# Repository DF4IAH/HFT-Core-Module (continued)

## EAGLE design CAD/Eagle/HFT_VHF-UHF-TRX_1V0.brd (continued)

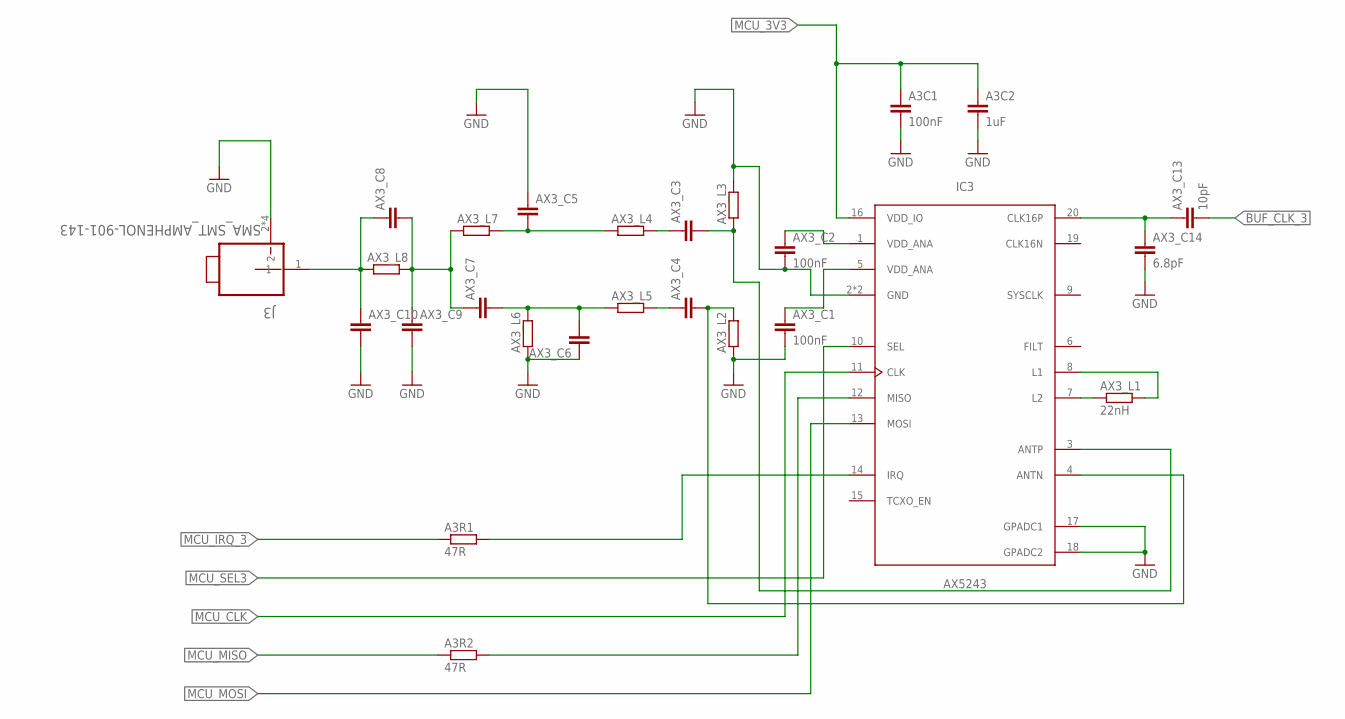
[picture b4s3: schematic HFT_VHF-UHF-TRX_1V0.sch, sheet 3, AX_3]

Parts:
A3C1: 100nF; C0805
A3C2: 1uF; C0805
A3R1, A3R2: 47R; R0805
AX3_C1, AX3_C2: 100nF; C0805
AX3_C3, AX3_C4, AX3_C5, AX3_C6, AX3_C7, AX3_C8, AX3_C9, AX3_C10: C-EUC0805; C0805
AX3_C13: 10pF; C0805
AX3_C14: 6.8pF; C0805
AX3_L1: 22nH; R0805
AX3_L2, AX3_L3, AX3_L4, AX3_L5, AX3_L6, AX3_L7, AX3_L8: R-EU_R0805; R0805
IC3: AX5243; QFN20-4X4-0P5-PAD
J3: SMA_SMT_AMPHENOL-901-143; SMA_SMT_AMPHENOL_901-143

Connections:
AX3_C3_L4: AX3_C3.1, AX3_L4.2
AX3_C4_L5: AX3_C4.1, AX3_L5.2
AX3_CH3_ANA1: AX3_C2.1, IC3.1 (VDD_ANA)
AX3_CH3_ANA2: AX3_C1.1, IC3.5 (VDD_ANA)
AX3_CH3_ANTN: AX3_C4.2, AX3_L2.2, IC3.4 (ANTN)
AX3_CH3_ANTP: AX3_C3.2, AX3_L3.1, IC3.3 (ANTP)
AX3_CH_3: AX3_C8.1, AX3_C10.1, AX3_L8.1, J3.1
AX3_IRQ_3: A3R1.2, IC3.14 (IRQ)
AX3_L1: AX3_L1.2, IC3.8 (L1)
AX3_L2: AX3_L1.1, IC3.7 (L2)
AX3_L4_C5_L7: AX3_C5.2, AX3_L4.1, AX3_L7.2
AX3_L4_C7_L8: AX3_C7.1, AX3_C8.2, AX3_C9.1, AX3_L7.1, AX3_L8.2
AX3_L5_C6_L6_C7: AX3_C6.2, AX3_C7.2, AX3_L5.1, AX3_L6.2
AX3_MISO: A3R2.2, IC3.12 (MISO)
BUF_CLK_3: AX3_C13.2; also elsewhere on the board
BUF_CLK_A3: AX3_C13.1, AX3_C14.1, IC3.20 (CLK16P)
GND: A3C1.2, A3C2.2, AX3_C1.2, AX3_C2.2, AX3_C5.1, AX3_C6.1, AX3_C9.2, AX3_C10.2, AX3_C14.2, AX3_L2.1, AX3_L3.2, AX3_L6.1, IC3.2 (GND), IC3.17 (GPADC1), IC3.18 (GPADC2), IC3.21 (GND), J3.2, J3.3 (2), J3.4 (2), J3.5 (2); also elsewhere on the board
MCU_3V3: A3C1.1, A3C2.1, IC3.16 (VDD_IO); also elsewhere on the board
MCU_CLK: IC3.11 (CLK); also elsewhere on the board
MCU_IRQ_3: A3R1.1; also elsewhere on the board
MCU_MISO: A3R2.1; also elsewhere on the board
MCU_MOSI: IC3.13 (MOSI); also elsewhere on the board
MCU_SEL3: IC3.10 (SEL); also elsewhere on the board

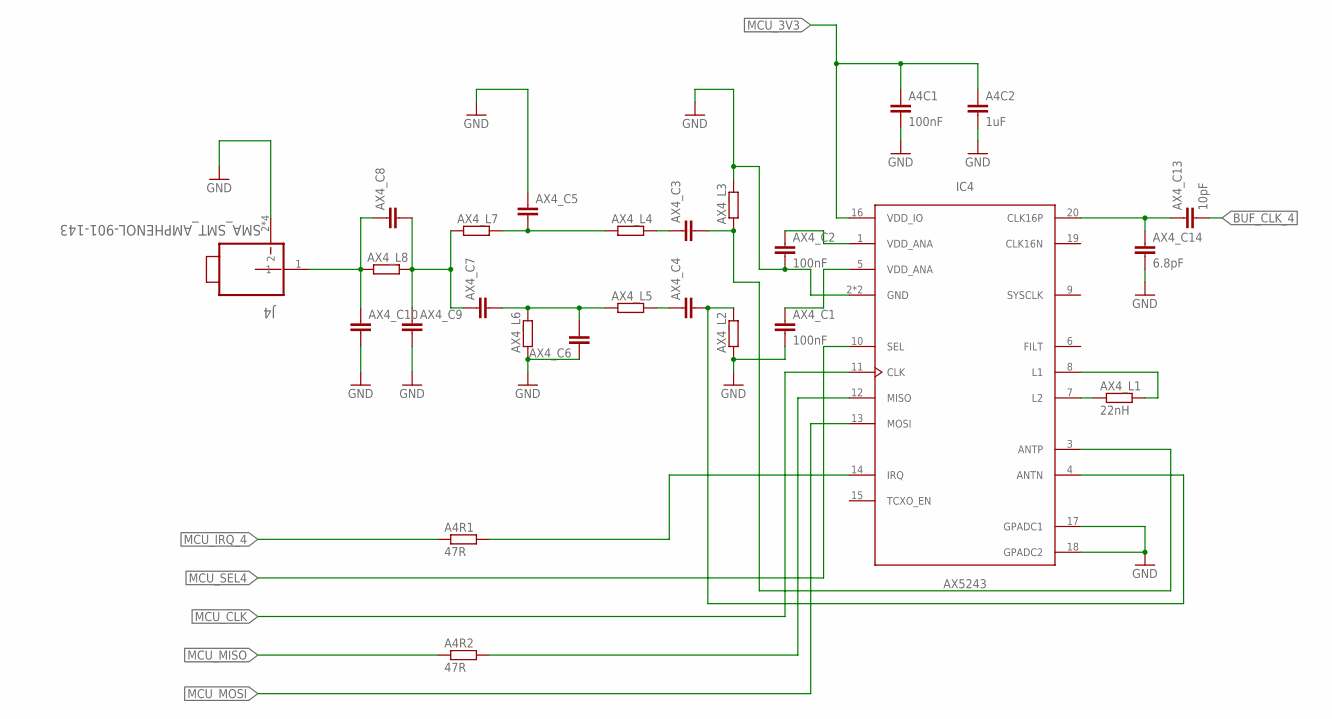
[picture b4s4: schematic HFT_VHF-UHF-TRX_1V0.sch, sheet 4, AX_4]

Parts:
A4C1: 100nF; C0805
A4C2: 1uF; C0805
A4R1, A4R2: 47R; R0805
AX4_C1, AX4_C2: 100nF; C0805
AX4_C3, AX4_C4, AX4_C5, AX4_C6, AX4_C7, AX4_C8, AX4_C9, AX4_C10: C-EUC0805; C0805
AX4_C13: 10pF; C0805
AX4_C14: 6.8pF; C0805
AX4_L1: 22nH; R0805
AX4_L2, AX4_L3, AX4_L4, AX4_L5, AX4_L6, AX4_L7, AX4_L8: R-EU_R0805; R0805
IC4: AX5243; QFN20-4X4-0P5-PAD
J4: SMA_SMT_AMPHENOL-901-143; SMA_SMT_AMPHENOL_901-143

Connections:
AX4_C3_L4: AX4_C3.1, AX4_L4.2
AX4_C4_L5: AX4_C4.1, AX4_L5.2
AX4_CH4_ANA1: AX4_C2.1, IC4.1 (VDD_ANA)
AX4_CH4_ANA2: AX4_C1.1, IC4.5 (VDD_ANA)
AX4_CH4_ANTN: AX4_C4.2, AX4_L2.2, IC4.4 (ANTN)
AX4_CH4_ANTP: AX4_C3.2, AX4_L3.1, IC4.3 (ANTP)
AX4_CH_4: AX4_C8.1, AX4_C10.1, AX4_L8.1, J4.1
AX4_IRQ_4: A4R1.2, IC4.14 (IRQ)
AX4_L1: AX4_L1.2, IC4.8 (L1)
AX4_L2: AX4_L1.1, IC4.7 (L2)
AX4_L4_C5_L7: AX4_C5.2, AX4_L4.1, AX4_L7.2
AX4_L4_C7_L8: AX4_C7.1, AX4_C8.2, AX4_C9.1, AX4_L7.1, AX4_L8.2
AX4_L5_C6_L6_C7: AX4_C6.2, AX4_C7.2, AX4_L5.1, AX4_L6.2
AX4_MISO: A4R2.2, IC4.12 (MISO)
BUF_CLK_4: AX4_C13.2; also elsewhere on the board
BUF_CLK_A4: AX4_C13.1, AX4_C14.1, IC4.20 (CLK16P)
GND: A4C1.2, A4C2.2, AX4_C1.2, AX4_C2.2, AX4_C5.1, AX4_C6.1, AX4_C9.2, AX4_C10.2, AX4_C14.2, AX4_L2.1, AX4_L3.2, AX4_L6.1, IC4.2 (GND), IC4.17 (GPADC1), IC4.18 (GPADC2), IC4.21 (GND), J4.2, J4.3 (2), J4.4 (2), J4.5 (2); also elsewhere on the board
MCU_3V3: A4C1.1, A4C2.1, IC4.16 (VDD_IO); also elsewhere on the board
MCU_CLK: IC4.11 (CLK); also elsewhere on the board
MCU_IRQ_4: A4R1.1; also elsewhere on the board
MCU_MISO: A4R2.1; also elsewhere on the board
MCU_MOSI: IC4.13 (MOSI); also elsewhere on the board
MCU_SEL4: IC4.10 (SEL); also elsewhere on the board

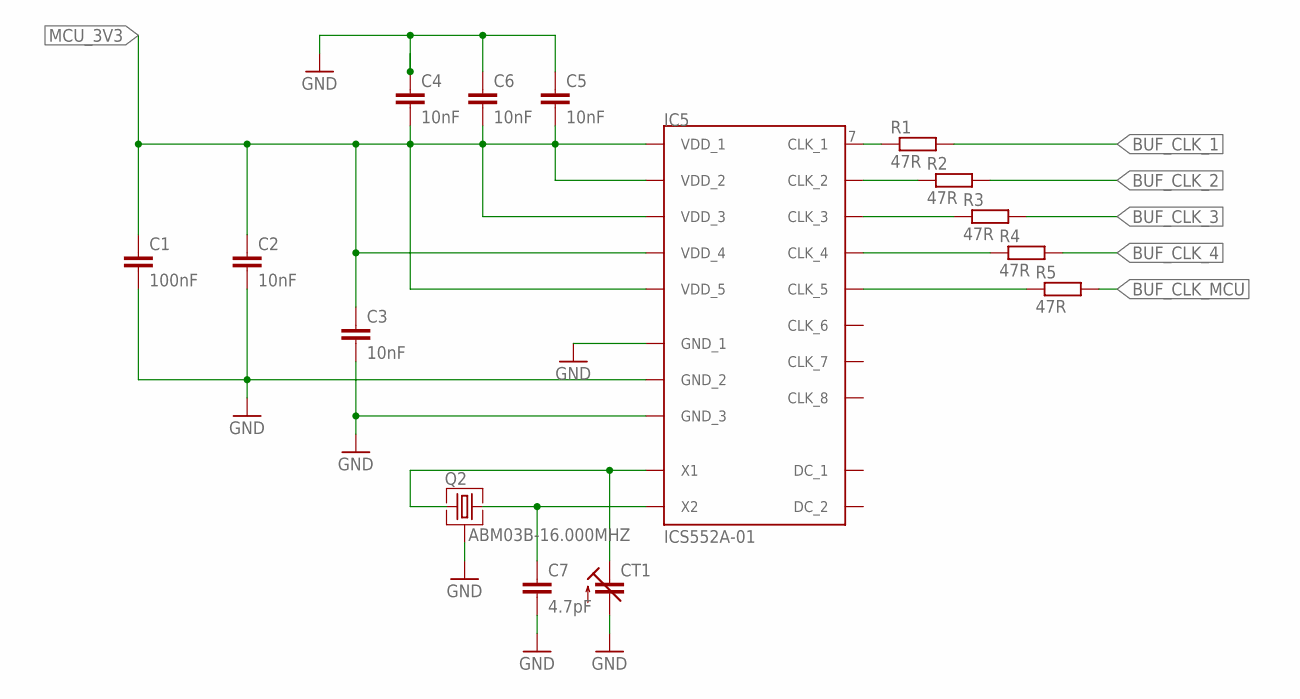
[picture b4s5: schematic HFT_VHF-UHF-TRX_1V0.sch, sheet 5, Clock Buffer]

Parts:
C1: 100nF; C0805
C2, C3, C4, C5, C6: 10nF; C0805
C7: 4.7pF; C0805
CT1: C-TRIMM3MM2_2MM5; 3MM2_X_2MM5
IC5: ICS552A-01; SSOP20
Q2: ABM03B-16.000MHZ; ABM03B
R1, R2, R3, R4, R5: 47R; R0805

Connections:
BUFF_X1: CT1.- (E), IC5.3 (X1), Q2.1
BUFF_X2: C7.1, IC5.2 (X2), Q2.3 (2)
BUF_CLK_1: R1.2; also elsewhere on the board
BUF_CLK_2: R2.2; also elsewhere on the board
BUF_CLK_3: R3.2; also elsewhere on the board
BUF_CLK_4: R4.2; also elsewhere on the board
BUF_CLK_MCU: R5.2; also elsewhere on the board
BUF_O_CLK_1: IC5.7 (CLK_1), R1.1
BUF_O_CLK_2: IC5.8 (CLK_2), R2.1
BUF_O_CLK_3: IC5.9 (CLK_3), R3.1
BUF_O_CLK_4: IC5.10 (CLK_4), R4.1
BUF_O_CLK_MCU: IC5.12 (CLK_5), R5.1
GND: C1.2, C2.2, C3.2, C4.1, C5.1, C6.1, C7.2, CT1.+ (A), IC5.5 (GND_1), IC5.6 (GND_2), IC5.14 (GND_3), Q2.2 (3), Q2.4 (3); also elsewhere on the board
MCU_3V3: C1.1, C2.1, C3.1, C4.2, C5.2, C6.2, IC5.4 (VDD_1), IC5.11 (VDD_2), IC5.15 (VDD_3), IC5.16 (VDD_4), IC5.20 (VDD_5); also elsewhere on the board

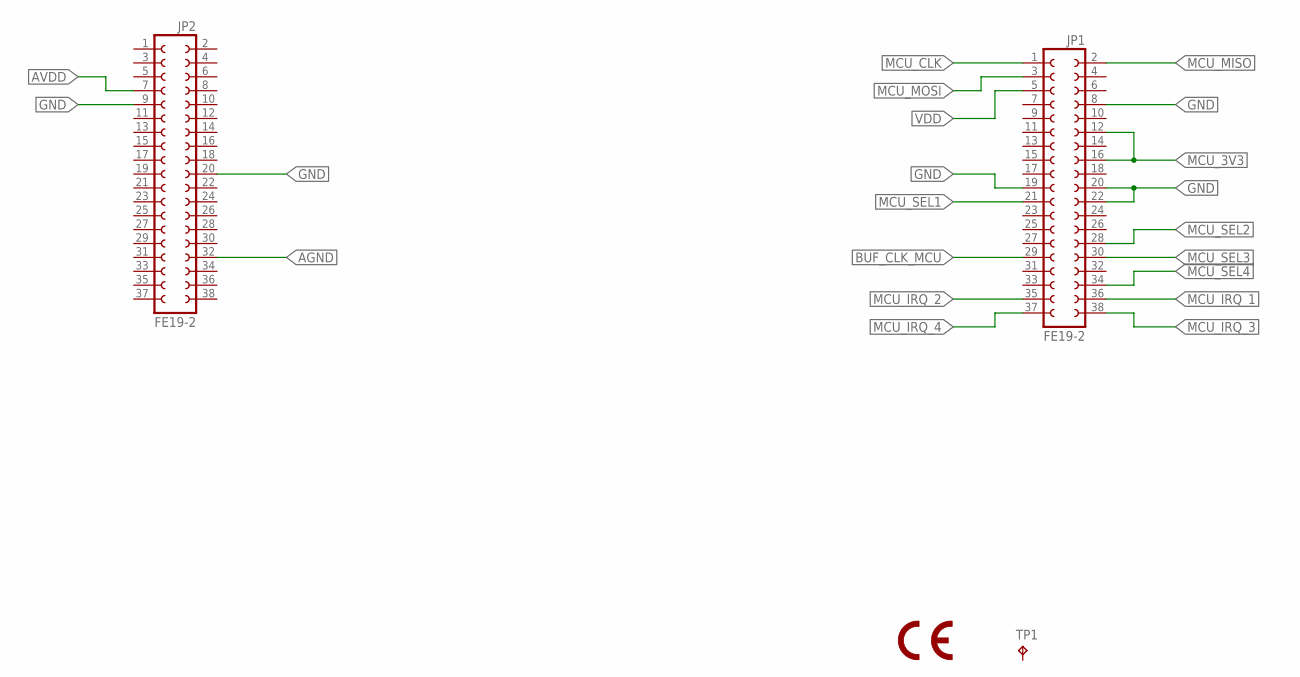
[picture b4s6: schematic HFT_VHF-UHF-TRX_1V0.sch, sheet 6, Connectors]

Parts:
JP1, JP2: FE19-2
TP1: TPB1,27; B1,27

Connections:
AGND: JP2.32
AVDD: JP2.7
BUF_CLK_MCU: JP1.29; also elsewhere on the board
GND: JP1.8, JP1.19, JP1.20, JP1.22, JP2.9, JP2.20; also elsewhere on the board
MCU_3V3: JP1.12, JP1.16; also elsewhere on the board
MCU_CLK: JP1.1; also elsewhere on the board
MCU_IRQ_1: JP1.36; also elsewhere on the board
MCU_IRQ_2: JP1.35; also elsewhere on the board
MCU_IRQ_3: JP1.38; also elsewhere on the board
MCU_IRQ_4: JP1.37; also elsewhere on the board
MCU_MISO: JP1.2; also elsewhere on the board
MCU_MOSI: JP1.3; also elsewhere on the board
MCU_SEL1: JP1.21; also elsewhere on the board
MCU_SEL2: JP1.28; also elsewhere on the board
MCU_SEL3: JP1.30; also elsewhere on the board
MCU_SEL4: JP1.34; also elsewhere on the board
VDD: JP1.5

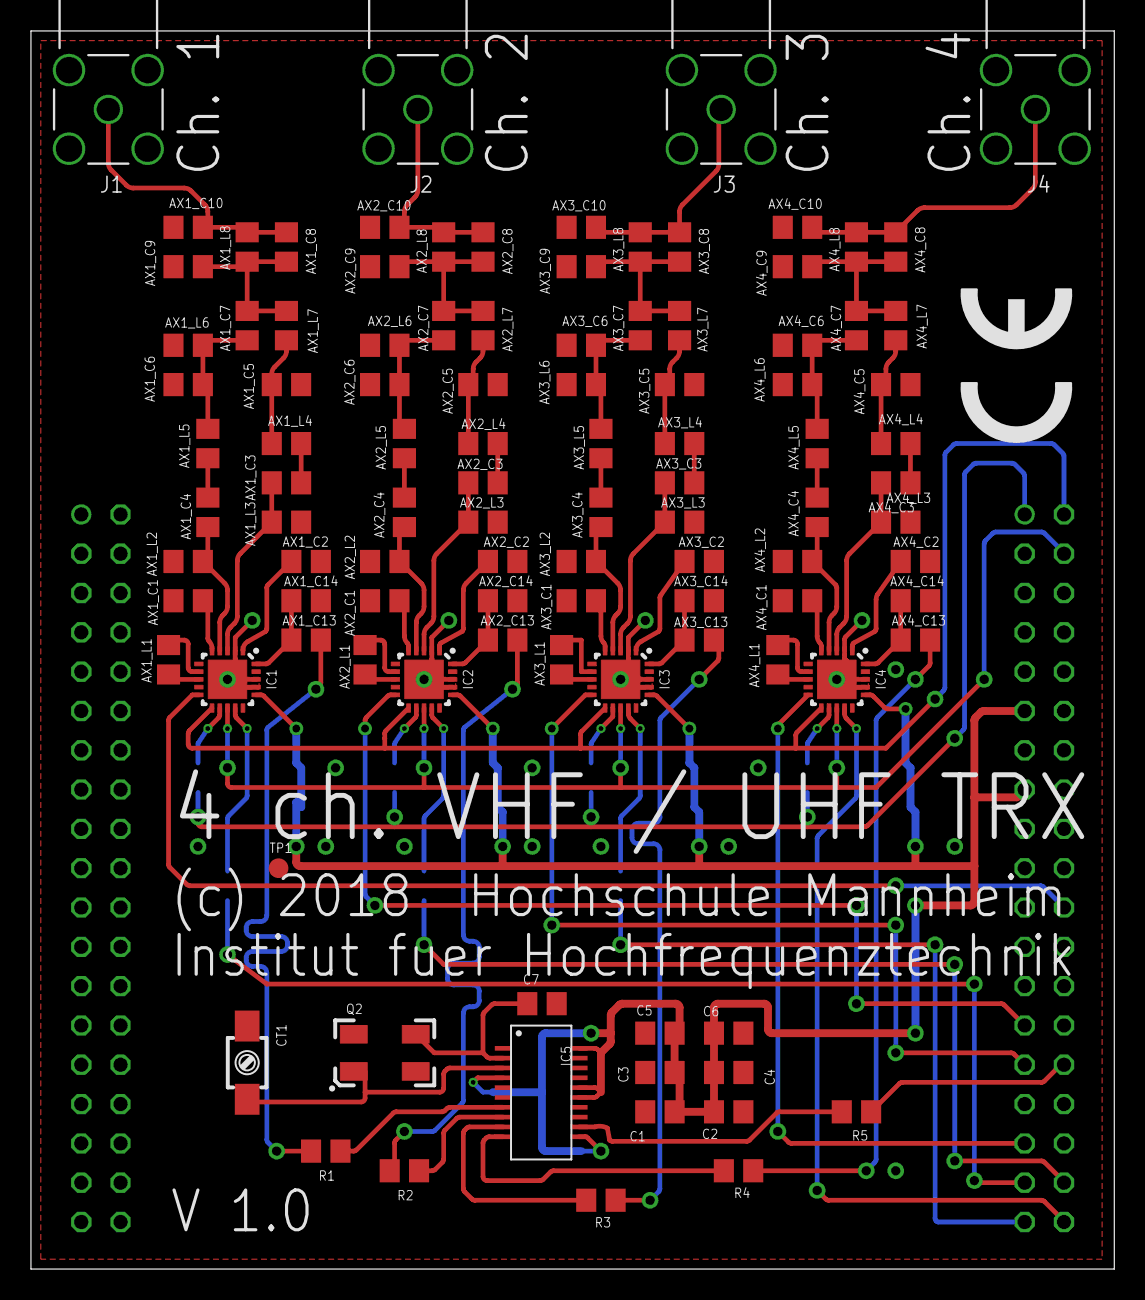
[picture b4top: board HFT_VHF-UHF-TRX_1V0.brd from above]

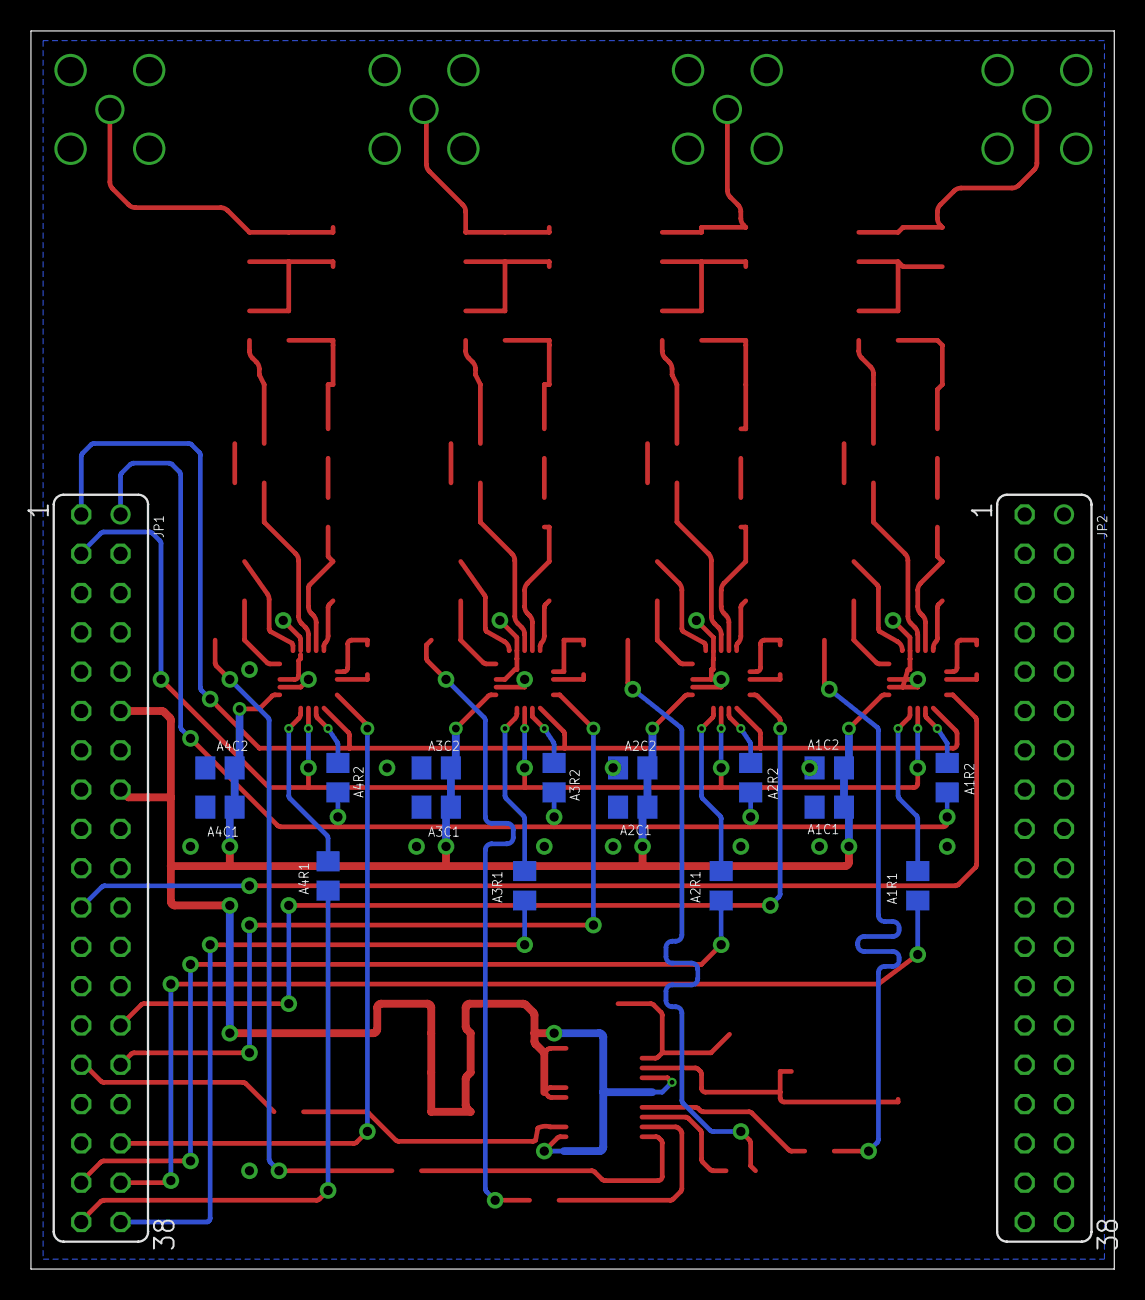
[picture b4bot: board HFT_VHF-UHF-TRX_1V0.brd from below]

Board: 2 copper layers, 70.0 x 80.0 mm, 123 parts (18 on the bottom side), 85 nets.

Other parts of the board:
X_CE_LOGO: CE_7.3MM

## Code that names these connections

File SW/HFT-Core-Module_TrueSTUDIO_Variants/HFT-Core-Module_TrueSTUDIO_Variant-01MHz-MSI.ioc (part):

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Mcu.Name=STM32L496ZGTxP
Mcu.Package=LQFP144
Mcu.UserName=STM32L496ZGTxP
PA0.GPIOParameters=GPIO_Speed,GPIO_PuPd,GPIO_Label
PA0.GPIO_Label=UART2_CTS_IN
PA0.GPIO_PuPd=GPIO_PULLDOWN
PA0.GPIO_Speed=GPIO_SPEED_FREQ_LOW
PA0.Mode=CTS_RTS
PA0.Signal=USART2_CTS
PA11.GPIOParameters=GPIO_Speed,GPIO_PuPd,GPIO_Label
PA11.GPIO_Label=PA_USB_N
PA11.GPIO_PuPd=GPIO_NOPULL
PA11.GPIO_Speed=GPIO_SPEED_FREQ_HIGH
PA11.Signal=USB_OTG_FS_DM
PA12.GPIOParameters=GPIO_Speed,GPIO_PuPd,GPIO_Label
PA12.GPIO_Label=PA_USB_P
PA12.GPIO_PuPd=GPIO_NOPULL
PA12.GPIO_Speed=GPIO_SPEED_FREQ_HIGH
PA12.Signal=USB_OTG_FS_DP
PA13\ (JTMS/SWDIO).GPIOParameters=GPIO_Label
PA13\ (JTMS/SWDIO).GPIO_Label=MCU_INOUT_SWDIO
PA13\ (JTMS/SWDIO).Mode=Serial_Wire
PA13\ (JTMS/SWDIO).Signal=SYS_JTMS-SWDIO
PA14\ (JTCK/SWCLK).GPIOParameters=GPIO_Label
PA14\ (JTCK/SWCLK).GPIO_Label=MCU_IN_SWCLK
PA14\ (JTCK/SWCLK).Mode=Serial_Wire
PA14\ (JTCK/SWCLK).Signal=SYS_JTCK-SWCLK
PA2.GPIOParameters=GPIO_Speed,GPIO_PuPd,GPIO_Label
PA2.GPIO_Label=UART2_TX_OUT
PA2.GPIO_PuPd=GPIO_NOPULL
PA2.GPIO_Speed=GPIO_SPEED_FREQ_LOW
PA2.Mode=Asynchronous
PA2.Signal=USART2_TX
PA3.GPIOParameters=GPIO_Label
PA3.GPIO_Label=MCU_VSOL_ADC1
PA3.Signal=ADCx_IN8
PA6.GPIOParameters=GPIO_Speed,GPIO_PuPd,GPIO_Label
PA6.GPIO_Label=UART3_CTS_IN
PA6.GPIO_PuPd=GPIO_PULLDOWN
PA6.GPIO_Speed=GPIO_SPEED_FREQ_LOW
PA6.Mode=CTS_RTS
PA6.Signal=USART3_CTS
PA7.GPIOParameters=GPIO_PuPd,GPIO_Label
PA7.GPIO_Label=MCU_OUT_PWM_LED_G
PA7.GPIO_PuPd=GPIO_NOPULL
PA7.Signal=S_TIM3_CH2
PA8.GPIOParameters=GPIO_Speed,GPIO_PuPd,GPIO_Label
PA8.GPIO_Label=MCU_MCO
PA8.GPIO_PuPd=GPIO_NOPULL
PA8.GPIO_Speed=GPIO_SPEED_FREQ_LOW
PA8.Mode=Clock-out
PA8.Signal=RCC_MCO
PA9.GPIOParameters=GPIO_PuPd,GPIO_Label
PA9.GPIO_Label=MCU_IN_VBUS
PA9.GPIO_PuPd=GPIO_PULLDOWN
PA9.Signal=USB_OTG_FS_VBUS
PB0.GPIOParameters=GPIO_PuPd,GPIO_Label
PB0.GPIO_Label=MCU_OUT_PWM_LED_B
PB0.GPIO_PuPd=GPIO_NOPULL
PB0.Signal=S_TIM3_CH3
PB1.GPIOParameters=GPIO_Speed,GPIO_PuPd,GPIO_Label
PB1.GPIO_Label=UART3_RTS_OUT
PB1.GPIO_PuPd=GPIO_NOPULL
PB1.GPIO_Speed=GPIO_SPEED_FREQ_LOW
PB1.Mode=CTS_RTS
PB1.Signal=USART3_RTS
PB10.GPIOParameters=GPIO_PuPd,GPIO_Label
PB10.GPIO_Label=MCU_IN_RE_I
PB10.GPIO_PuPd=GPIO_PULLUP
PB10.Signal=GPIO_Input
PB12.GPIOParameters=GPIO_PuPd,GPIO_Label
PB12.GPIO_Label=MCU_IN_RE_Q
PB12.GPIO_PuPd=GPIO_PULLUP
PB12.Signal=GPIO_Input
PB13.GPIOParameters=GPIO_Speed,GPIO_PuPd,GPIO_Label
PB13.GPIO_Label=I2S2A_SCK_IN
PB13.GPIO_PuPd=GPIO_PULLDOWN
PB13.GPIO_Speed=GPIO_SPEED_FREQ_MEDIUM
PB13.Signal=SAI2_SCK_A
PB14.GPIOParameters=GPIO_PuPd,GPIO_Label
PB14.GPIO_Label=MCU_IN_RE_PB
PB14.GPIO_PuPd=GPIO_PULLUP
PB14.Signal=GPIO_Input
PB3\ (JTDO/TRACESWO).GPIOParameters=GPIO_PuPd,GPIO_Label
PB3\ (JTDO/TRACESWO).GPIO_Label=MCU_INOUT_PN00
PB3\ (JTDO/TRACESWO).GPIO_PuPd=GPIO_PULLDOWN
PB3\ (JTDO/TRACESWO).Signal=GPIO_Input
PB5.GPIOParameters=GPIO_PuPd,GPIO_Label
PB5.GPIO_Label=MCU_INOUT_PN01
PB5.GPIO_PuPd=GPIO_PULLDOWN
PB5.Signal=GPIO_Input
PB6.GPIOParameters=GPIO_PuPd,GPIO_Label
PB6.GPIO_Label=MCU_INOUT_PN02
PB6.GPIO_PuPd=GPIO_PULLDOWN
PB6.Signal=GPIO_Input
PB7.GPIOParameters=GPIO_PuPd,GPIO_Label
PB7.GPIO_Label=MCU_INOUT_PN03
PB7.GPIO_PuPd=GPIO_PULLDOWN
PB7.Signal=GPIO_Input
PC0.GPIOParameters=GPIO_PuPd,GPIO_Label
PC0.GPIO_Label=MCU_OUT_VDD12_EN
PC0.GPIO_PuPd=GPIO_NOPULL
PC0.Signal=GPIO_Output
PC1.GPIOParameters=GPIO_PuPd,GPIO_Label
PC1.GPIO_Label=MCU_OUT_HICUR_EN
PC1.GPIO_PuPd=GPIO_NOPULL
PC1.Signal=GPIO_Output
PC10.GPIOParameters=GPIO_Speed,GPIO_PuPd,GPIO_Label
PC10.GPIO_Label=MCU_SPI3_SCK
PC10.GPIO_PuPd=GPIO_NOPULL
PC10.GPIO_Speed=GPIO_SPEED_FREQ_VERY_HIGH
PC10.Mode=Full_Duplex_Master
PC10.Signal=SPI3_SCK
PC11.GPIOParameters=GPIO_Speed,GPIO_PuPd,GPIO_Label
PC11.GPIO_Label=MCU_SPI3_MISO
PC11.GPIO_PuPd=GPIO_PULLDOWN
PC11.GPIO_Speed=GPIO_SPEED_FREQ_VERY_HIGH
PC11.Mode=Full_Duplex_Master
PC11.Signal=SPI3_MISO
PC12.GPIOParameters=GPIO_Speed,GPIO_PuPd,GPIO_Label
PC12.GPIO_Label=MCU_SPI3_MOSI
PC12.GPIO_PuPd=GPIO_NOPULL
PC12.GPIO_Speed=GPIO_SPEED_FREQ_VERY_HIGH
PC12.Mode=Full_Duplex_Master
PC12.Signal=SPI3_MOSI
PC13.GPIOParameters=GPIO_Label
PC13.GPIO_Label=MCU_IN_WAKEUP
PC13.Mode=SYS_WakeUp1
PC13.Signal=SYS_WKUP2
PC14-OSC32_IN\ (PC14).GPIOParameters=GPIO_Label
PC14-OSC32_IN\ (PC14).GPIO_Label=MCU_OSC32_IN
PC14-OSC32_IN\ (PC14).Mode=LSE-External-Oscillator
PC14-OSC32_IN\ (PC14).Signal=RCC_OSC32_IN
PC15-OSC32_OUT\ (PC15).GPIOParameters=GPIO_Label
PC15-OSC32_OUT\ (PC15).GPIO_Label=MCU_OSC32_OUT
PC15-OSC32_OUT\ (PC15).Mode=LSE-External-Oscillator
PC15-OSC32_OUT\ (PC15).Signal=RCC_OSC32_OUT
PC2.GPIOParameters=GPIO_PuPd,GPIO_Label
PC2.GPIO_Label=MCU_OUT_VUSB_EN
PC2.GPIO_PuPd=GPIO_NOPULL
PC2.Signal=GPIO_Output
PC3.GPIOParameters=GPIO_PuPd,GPIO_Label
PC3.GPIO_Label=MCU_OUT_20MHZ_EN
PC3.GPIO_PuPd=GPIO_NOPULL
PC3.Signal=GPIO_Output
PC4.GPIOParameters=GPIO_Speed,GPIO_PuPd,GPIO_Label
PC4.GPIO_Label=UART3_TX_OUT
PC4.GPIO_PuPd=GPIO_NOPULL
PC4.GPIO_Speed=GPIO_SPEED_FREQ_LOW
PC4.Mode=Asynchronous
PC4.Signal=USART3_TX
PC5.GPIOParameters=GPIO_Speed,GPIO_PuPd,GPIO_Label
PC5.GPIO_Label=UART3_RX_IN
PC5.GPIO_PuPd=GPIO_PULLUP
PC5.GPIO_Speed=GPIO_SPEED_FREQ_LOW
PC5.Mode=Asynchronous
PC5.Signal=USART3_RX
PC6.GPIOParameters=GPIO_PuPd,GPIO_Label
PC6.GPIO_Label=MCU_OUT_PWM_LED_R
PC6.GPIO_PuPd=GPIO_NOPULL
PC6.Signal=S_TIM3_CH1
PC8.GPIOParameters=GPIO_PuPd,GPIO_Label
PC8.GPIO_Label=MCU_IN_AUDIO_DAC_nRDY
PC8.GPIO_PuPd=GPIO_PULLUP
PC8.Signal=GPIO_Input
PC9.GPIOParameters=GPIO_Speed,PinState,GPIO_PuPd,GPIO_Label
PC9.GPIO_Label=MCU_OUT_AUDIO_DAC_SEL
PC9.GPIO_PuPd=GPIO_NOPULL
PC9.GPIO_Speed=GPIO_SPEED_FREQ_VERY_HIGH
PC9.PinState=GPIO_PIN_RESET
PC9.Signal=GPIO_Output
PD0.GPIOParameters=GPIO_PuPd,GPIO_Label
PD0.GPIO_Label=MCU_IN_AUDIO_ADC_MDAT1
PD0.GPIO_PuPd=GPIO_PULLDOWN
PD0.Signal=GPIO_Input
PD1.GPIOParameters=GPIO_PuPd,GPIO_Label
PD1.GPIO_Label=MCU_IN_AUDIO_ADC_MDAT0
PD1.GPIO_PuPd=GPIO_PULLDOWN
PD1.Signal=GPIO_Input
PD10.GPIOParameters=GPIO_PuPd,GPIO_Label
PD10.GPIO_Label=MCU_INOUT_PS01
PD10.GPIO_PuPd=GPIO_PULLDOWN
PD10.Signal=GPIO_Input
PD11.GPIOParameters=GPIO_Speed,GPIO_PuPd,GPIO_Label
PD11.GPIO_Label=I2S2A_SD_IN
PD11.GPIO_PuPd=GPIO_PULLDOWN
PD11.GPIO_Speed=GPIO_SPEED_FREQ_MEDIUM
PD11.Signal=SAI2_SD_A
PD12.GPIOParameters=GPIO_Speed,GPIO_PuPd,GPIO_Label
PD12.GPIO_Label=I2S2A_FS_IN
PD12.GPIO_PuPd=GPIO_PULLDOWN
PD12.GPIO_Speed=GPIO_SPEED_FREQ_MEDIUM
PD12.Signal=SAI2_FS_A
PD13.GPIOParameters=GPIO_Speed,GPIO_PuPdOD,GPIO_Label
PD13.GPIO_Label=MCU_I2C4_SDA
PD13.GPIO_PuPdOD=GPIO_PULLUP
PD13.GPIO_Speed=GPIO_SPEED_FREQ_LOW
PD13.Mode=I2C
PD13.Signal=I2C4_SDA
PD14.GPIOParameters=GPIO_PuPd,GPIO_Label
PD14.GPIO_Label=MCU_INOUT_PS02
PD14.GPIO_PuPd=GPIO_PULLDOWN
PD14.Signal=GPIO_Input
PD15.GPIOParameters=GPIO_PuPd,GPIO_Label
PD15.GPIO_Label=MCU_INOUT_PS03
PD15.GPIO_PuPd=GPIO_PULLDOWN
PD15.Signal=GPIO_Input
PD2.GPIOParameters=GPIO_PuPd,GPIO_Label
PD2.GPIO_Label=MCU_IN_AUDIO_ADC_nDR
PD2.GPIO_PuPd=GPIO_PULLUP
PD2.Signal=GPIO_Input
PD3.GPIOParameters=GPIO_PuPd,GPIO_Label
PD3.GPIO_Label=MCU_OUT_AUDIO_ADC_nRESET
PD3.GPIO_PuPd=GPIO_NOPULL
PD3.Signal=GPIO_Output
PD4.GPIOParameters=GPIO_Speed,GPIO_PuPd,GPIO_Label
PD4.GPIO_Label=UART2_RTS_OUT
PD4.GPIO_PuPd=GPIO_NOPULL
PD4.GPIO_Speed=GPIO_SPEED_FREQ_LOW
PD4.Mode=CTS_RTS
PD4.Signal=USART2_RTS
PD5.GPIOParameters=GPIO_Speed,PinState,GPIO_PuPd,GPIO_Label
PD5.GPIO_Label=MCU_OUT_AUDIO_ADC_SEL
PD5.GPIO_PuPd=GPIO_NOPULL
PD5.GPIO_Speed=GPIO_SPEED_FREQ_VERY_HIGH
PD5.PinState=GPIO_PIN_RESET
PD5.Signal=GPIO_Output
PD6.GPIOParameters=GPIO_Speed,GPIO_PuPd,GPIO_Label
PD6.GPIO_Label=UART2_RX_IN
PD6.GPIO_PuPd=GPIO_PULLUP
PD6.GPIO_Speed=GPIO_SPEED_FREQ_LOW
PD6.Mode=Asynchronous
PD6.Signal=USART2_RX
PD7.GPIOParameters=GPIO_PuPd,GPIO_Label
PD7.GPIO_Label=MCU_IN_EXTI7_INTR_SI5338
PD7.GPIO_PuPd=GPIO_PULLDOWN
PD7.Signal=GPXTI7
PD8.GPIOParameters=GPIO_PuPd,GPIO_Label
PD8.GPIO_Label=MCU_OUT_SX_nRESET
PD8.GPIO_PuPd=GPIO_NOPULL
PD8.Signal=GPIO_Output
PD9.GPIOParameters=GPIO_PuPd,GPIO_Label
PD9.GPIO_Label=MCU_INOUT_PS00
PD9.GPIO_PuPd=GPIO_PULLDOWN
PD9.Signal=GPIO_Input
PE0.GPIOParameters=GPIO_PuPd,GPIO_Label
PE0.GPIO_Label=MCU_EVENTOUT_PE0
PE0.GPIO_PuPd=GPIO_NOPULL
PE0.Signal=EVENTOUT
PE10.GPIOParameters=GPIO_Speed,GPIO_PuPd,GPIO_Label
PE10.GPIO_Label=I2S1B_MCLK_OUT
PE10.GPIO_PuPd=GPIO_NOPULL
PE10.GPIO_Speed=GPIO_SPEED_FREQ_MEDIUM
PE10.Signal=SAI1_MCLK_B
PE11.GPIOParameters=GPIO_Speed,PinState,GPIO_PuPd,GPIO_Label
PE11.GPIO_Label=MCU_OUT_AX_SEL
PE11.GPIO_PuPd=GPIO_NOPULL
PE11.GPIO_Speed=GPIO_SPEED_FREQ_VERY_HIGH
PE11.PinState=GPIO_PIN_SET
PE11.Signal=GPIO_Output
PE12.GPIOParameters=GPIO_Speed,PinState,GPIO_PuPd,GPIO_Label
PE12.GPIO_Label=MCU_OUT_SX_SEL
PE12.GPIO_PuPd=GPIO_NOPULL
PE12.GPIO_Speed=GPIO_SPEED_FREQ_VERY_HIGH
PE12.PinState=GPIO_PIN_SET
PE12.Signal=GPIO_Output
PE13.GPIOParameters=GPIO_Speed,GPIO_PuPd,GPIO_Label
PE13.GPIO_Label=MCU_SPI1_SCK
PE13.GPIO_PuPd=GPIO_NOPULL
PE13.GPIO_Speed=GPIO_SPEED_FREQ_VERY_HIGH
PE13.Mode=Full_Duplex_Master
PE13.Signal=SPI1_SCK
PE14.GPIOParameters=GPIO_Speed,GPIO_PuPd,GPIO_Label
PE14.GPIO_Label=MCU_SPI1_MISO
PE14.GPIO_PuPd=GPIO_PULLDOWN
PE14.GPIO_Speed=GPIO_SPEED_FREQ_VERY_HIGH

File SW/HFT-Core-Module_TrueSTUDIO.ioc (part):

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Mcu.Name=STM32L496ZGTxP
Mcu.Package=LQFP144
Mcu.UserName=STM32L496ZGTxP
PA0.GPIOParameters=GPIO_Label
PA0.GPIO_Label=MCU_ADC1_IN5_VSOL
PA0.Signal=ADCx_IN5
PA1.GPIOParameters=GPIO_Label
PA1.GPIO_Label=MCU_ADC1_IN6_XO_PULL
PA1.Signal=ADCx_IN6
PA10.GPIOParameters=GPIO_Label
PA10.GPIO_Label=MCU_USB_OTG_FS_ID
PA10.Mode=OTG/Dual_Role_Device
PA10.Signal=USB_OTG_FS_ID
PA11.GPIOParameters=GPIO_Speed,GPIO_PuPd,GPIO_Label
PA11.GPIO_Label=MCU_USB_OTG_FS_DM
PA11.GPIO_PuPd=GPIO_NOPULL
PA11.GPIO_Speed=GPIO_SPEED_FREQ_HIGH
PA11.Mode=OTG/Dual_Role_Device
PA11.Signal=USB_OTG_FS_DM
PA12.GPIOParameters=GPIO_Speed,GPIO_PuPd,GPIO_Label
PA12.GPIO_Label=MCU_USB_OTG_FS_DP
PA12.GPIO_PuPd=GPIO_NOPULL
PA12.GPIO_Speed=GPIO_SPEED_FREQ_HIGH
PA12.Mode=OTG/Dual_Role_Device
PA12.Signal=USB_OTG_FS_DP
PA13\ (JTMS/SWDIO).GPIOParameters=GPIO_Label
PA13\ (JTMS/SWDIO).GPIO_Label=MCU_SWDIO
PA13\ (JTMS/SWDIO).Mode=Serial_Wire
PA13\ (JTMS/SWDIO).Signal=SYS_JTMS-SWDIO
PA14\ (JTCK/SWCLK).GPIOParameters=GPIO_Label
PA14\ (JTCK/SWCLK).GPIO_Label=MCU_SWCLK
PA14\ (JTCK/SWCLK).Mode=Serial_Wire
PA14\ (JTCK/SWCLK).Signal=SYS_JTCK-SWCLK
PA2.GPIOParameters=GPIO_Label
PA2.GPIO_Label=MCU_LPUART_TX_OUT
PA2.Mode=Asynchronous
PA2.Signal=LPUART1_TX
PA3.GPIOParameters=GPIO_Label
PA3.GPIO_Label=MCU_ADC1_IN8_LIPO_CUR
PA3.Signal=ADCx_IN8
PA4.GPIOParameters=GPIO_Label
PA4.GPIO_Label=MCU_LIPO_CEN_OUT
PA4.Signal=GPIO_Output
PA5.GPIOParameters=GPIO_Label
PA5.GPIO_Label=MCU_EXTI5_LIPO
PA5.Signal=GPXTI5
PA6.GPIOParameters=GPIO_Label
PA6.GPIO_Label=MCU_LPUART_CTS_IN
PA6.Mode=CTS_RTS
PA6.Signal=LPUART1_CTS
PA7.GPIOParameters=GPIO_PuPd,GPIO_Label
PA7.GPIO_Label=MCU_PWM_LED_G
PA7.GPIO_PuPd=GPIO_NOPULL
PA7.Signal=S_TIM3_CH2
PA8.GPIOParameters=GPIO_Speed,GPIO_PuPd,GPIO_Label
PA8.GPIO_Label=MCU_MCO
PA8.GPIO_PuPd=GPIO_NOPULL
PA8.GPIO_Speed=GPIO_SPEED_FREQ_LOW
PA8.Mode=Clock-out
PA8.Signal=RCC_MCO
PA9.GPIOParameters=GPIO_PuPd,GPIO_Label
PA9.GPIO_Label=MCU_USB_OTG_FS_VBUS
PA9.GPIO_PuPd=GPIO_PULLDOWN
PA9.Mode=Activate_VBUS
PA9.Signal=USB_OTG_FS_VBUS
PB0.GPIOParameters=GPIO_PuPd,GPIO_Label
PB0.GPIO_Label=MCU_PWM_LED_B
PB0.GPIO_PuPd=GPIO_NOPULL
PB0.Signal=S_TIM3_CH3
PB1.GPIOParameters=GPIO_Label
PB1.GPIO_Label=MCU_LPUART_RTS_OUT
PB1.Mode=CTS_RTS
PB1.Signal=LPUART1_RTS
PB13.GPIOParameters=GPIO_Speed,GPIO_PuPd,GPIO_Label
PB13.GPIO_Label=MCU_I2S2A_SCK_IN
PB13.GPIO_PuPd=GPIO_PULLDOWN
PB13.GPIO_Speed=GPIO_SPEED_FREQ_MEDIUM
PB13.Mode=SAI_A_AsyncSlave
PB13.Signal=SAI2_SCK_A
PB15.GPIOParameters=GPIO_Label
PB15.GPIO_Label=MCU_SPI2_MOSI
PB15.Mode=Full_Duplex_Master
PB15.Signal=SPI2_MOSI
PB2.GPIOParameters=GPIO_Label
PB2.GPIO_Label=MCU_SW_PWR_OUT
PB2.Signal=GPIO_Output
PB3\ (JTDO/TRACESWO).GPIOParameters=GPIO_PuPd,GPIO_Label
PB3\ (JTDO/TRACESWO).GPIO_Label=MCU_PN00_INOUT
PB3\ (JTDO/TRACESWO).GPIO_PuPd=GPIO_PULLDOWN
PB3\ (JTDO/TRACESWO).Signal=GPIO_Input
PB5.GPIOParameters=GPIO_PuPd,GPIO_Label
PB5.GPIO_Label=MCU_PN01_INOUT
PB5.GPIO_PuPd=GPIO_PULLDOWN
PB5.Signal=GPIO_Input
PB6.GPIOParameters=GPIO_PuPd,GPIO_Label
PB6.GPIO_Label=MCU_PN02_INOUT
PB6.GPIO_PuPd=GPIO_PULLDOWN
PB6.Signal=GPIO_Input
PB7.GPIOParameters=GPIO_PuPd,GPIO_Label
PB7.GPIO_Label=MCU_PN03_INOUT
PB7.GPIO_PuPd=GPIO_PULLDOWN
PB7.Signal=GPIO_Input
PC1.Mode=Dual Bank
PC1.Signal=QUADSPI_BK2_IO0
PC10.GPIOParameters=GPIO_Speed,GPIO_PuPd,GPIO_Label
PC10.GPIO_Label=MCU_SPI3_SCK
PC10.GPIO_PuPd=GPIO_NOPULL
PC10.GPIO_Speed=GPIO_SPEED_FREQ_VERY_HIGH
PC10.Mode=Full_Duplex_Master
PC10.Signal=SPI3_SCK
PC11.GPIOParameters=GPIO_Speed,GPIO_PuPd,GPIO_Label
PC11.GPIO_Label=MCU_SPI3_MISO
PC11.GPIO_PuPd=GPIO_PULLDOWN
PC11.GPIO_Speed=GPIO_SPEED_FREQ_VERY_HIGH
PC11.Mode=Full_Duplex_Master
PC11.Signal=SPI3_MISO
PC12.GPIOParameters=GPIO_Speed,GPIO_PuPd,GPIO_Label
PC12.GPIO_Label=MCU_SPI3_MOSI
PC12.GPIO_PuPd=GPIO_NOPULL
PC12.GPIO_Speed=GPIO_SPEED_FREQ_VERY_HIGH
PC12.Mode=Full_Duplex_Master
PC12.Signal=SPI3_MOSI
PC13.GPIOParameters=GPIO_Label
PC13.GPIO_Label=MCU_WAKEUP_IN
PC13.Mode=SYS_WakeUp1
PC13.Signal=SYS_WKUP2
PC14-OSC32_IN\ (PC14).GPIOParameters=GPIO_Label
PC14-OSC32_IN\ (PC14).GPIO_Label=MCU_OSC32_IN
PC14-OSC32_IN\ (PC14).Mode=LSE-External-Oscillator
PC14-OSC32_IN\ (PC14).Signal=RCC_OSC32_IN
PC15-OSC32_OUT\ (PC15).GPIOParameters=GPIO_Label
PC15-OSC32_OUT\ (PC15).GPIO_Label=MCU_OSC32_OUT
PC15-OSC32_OUT\ (PC15).Mode=LSE-External-Oscillator
PC15-OSC32_OUT\ (PC15).Signal=RCC_OSC32_OUT
PC2.Mode=Dual Bank
PC2.Signal=QUADSPI_BK2_IO1
PC3.Mode=Dual Bank
PC3.Signal=QUADSPI_BK2_IO2
PC5.GPIOParameters=GPIO_Label
PC5.GPIO_Label=MCU_BNO085_PS0_WAKE_OUT
PC5.Signal=GPIO_Output
PC6.GPIOParameters=GPIO_PuPd,GPIO_Label
PC6.GPIO_Label=MCU_PWM_LED_R
PC6.GPIO_PuPd=GPIO_NOPULL
PC6.Signal=S_TIM3_CH1
PC7.GPIOParameters=GPIO_Label
PC7.GPIO_Label=MCU_LPUART_DCD_IN
PC7.Signal=GPIO_Input
PC8.GPIOParameters=GPIO_Label
PC8.GPIO_Label=MCU_EINK_BUSY_IN
PC8.Signal=GPIO_Input
PC9.GPIOParameters=GPIO_Label
PC9.GPIO_Label=MCU_EXTI9_SI5338
PC9.Signal=GPXTI9
PD1.GPIOParameters=GPIO_Label
PD1.GPIO_Label=MCU_SPI2_SCK
PD1.Mode=Full_Duplex_Master
PD1.Signal=SPI2_SCK
PD10.GPIOParameters=GPIO_PuPd,GPIO_Label
PD10.GPIO_Label=MCU_PS01_INOUT
PD10.GPIO_PuPd=GPIO_PULLDOWN
PD10.Signal=GPIO_Input
PD11.GPIOParameters=GPIO_Speed,GPIO_PuPd,GPIO_Label
PD11.GPIO_Label=MCU_I2S2A_SD_IN
PD11.GPIO_PuPd=GPIO_PULLDOWN
PD11.GPIO_Speed=GPIO_SPEED_FREQ_MEDIUM
PD11.Mode=SAI_A_AsyncSlave
PD11.Signal=SAI2_SD_A
PD12.GPIOParameters=GPIO_Speed,GPIO_PuPd,GPIO_Label
PD12.GPIO_Label=MCU_I2S2A_FS_IN
PD12.GPIO_PuPd=GPIO_PULLDOWN
PD12.GPIO_Speed=GPIO_SPEED_FREQ_MEDIUM
PD12.Mode=SAI_A_AsyncSlave
PD12.Signal=SAI2_FS_A
PD14.GPIOParameters=GPIO_PuPd,GPIO_Label
PD14.GPIO_Label=MCU_PS02_INOUT
PD14.GPIO_PuPd=GPIO_PULLDOWN
PD14.Signal=GPIO_Input
PD15.GPIOParameters=GPIO_PuPd,GPIO_Label
PD15.GPIO_Label=MCU_PS03_INOUT
PD15.GPIO_PuPd=GPIO_PULLDOWN
PD15.Signal=GPIO_Input
PD2.GPIOParameters=GPIO_Label
PD2.GPIO_Label=MCU_EXTI2_AUDIO_ADC
PD2.Signal=GPXTI2
PD3.GPIOParameters=GPIO_PuPd,GPIO_Label
PD3.GPIO_Label=MCU_SPI2_MISO
PD3.GPIO_PuPd=GPIO_PULLDOWN
PD3.Mode=Full_Duplex_Master
PD3.Signal=SPI2_MISO
PD7.Mode=Dual Bank
PD7.Signal=QUADSPI_BK2_IO3
PD8.GPIOParameters=GPIO_Label
PD8.GPIO_Label=MCU_SX_BUSY_IN
PD8.Signal=GPIO_Input
PD9.GPIOParameters=GPIO_PuPd,GPIO_Label
PD9.GPIO_Label=MCU_PS00_INOUT
PD9.GPIO_PuPd=GPIO_PULLDOWN
PD9.Signal=GPIO_Input
PE10.GPIOParameters=GPIO_Speed,GPIO_PuPd,GPIO_Label
PE10.GPIO_Label=MCU_I2S1B_MCLK_OUT
PE10.GPIO_PuPd=GPIO_NOPULL
PE10.GPIO_Speed=GPIO_SPEED_FREQ_MEDIUM
PE10.Mode=SAI_B_MasterWithClock
PE10.Signal=SAI1_MCLK_B
PE11.GPIOParameters=GPIO_Label
PE11.GPIO_Label=QUADSPI_BK12_NCS
PE11.Mode=Enable Chip Select 1 for both banks
PE11.Signal=QUADSPI_BK1_NCS
PE12.Mode=Dual Bank
PE12.Signal=QUADSPI_BK1_IO0
PE13.Mode=Dual Bank
PE13.Signal=QUADSPI_BK1_IO1
PE14.Mode=Dual Bank
PE14.Signal=QUADSPI_BK1_IO2
PE15.Mode=Dual Bank
PE15.Signal=QUADSPI_BK1_IO3
PE3.GPIOParameters=GPIO_Speed,GPIO_PuPd,GPIO_Label
PE3.GPIO_Label=MCU_I2S1B_SD_OUT
PE3.GPIO_PuPd=GPIO_NOPULL
PE3.GPIO_Speed=GPIO_SPEED_FREQ_MEDIUM
PE3.Mode=SAI_B_MasterWithClock
PE3.Signal=SAI1_SD_B
PE4.GPIOParameters=GPIO_Label
PE4.GPIO_Label=MCU_BQ_EN_OUT
PE4.Signal=GPIO_Output
PE5.GPIOParameters=PinState,GPIO_Label
PE5.GPIO_Label=MCU_TPS_EN_OUT
PE5.PinState=GPIO_PIN_SET
PE5.Signal=GPIO_Output
PE6.GPIOParameters=GPIO_Label
PE6.GPIO_Label=MCU_PWM_LCD_BL
PE6.Signal=S_TIM3_CH4
PE7.GPIOParameters=GPIO_Label
PE7.GPIO_Label=MCU_EXTI7_AX
PE7.Signal=GPXTI7
PE8.GPIOParameters=GPIO_Speed,GPIO_PuPd,GPIO_Label
PE8.GPIO_Label=MCU_I2S1B_SCK_OUT
PE8.GPIO_PuPd=GPIO_NOPULL
PE8.GPIO_Speed=GPIO_SPEED_FREQ_MEDIUM
PE8.Mode=SAI_B_MasterWithClock
PE8.Signal=SAI1_SCK_B
PE9.GPIOParameters=GPIO_Speed,GPIO_PuPd,GPIO_Label
PE9.GPIO_Label=MCU_I2S1B_FS_OUT
PE9.GPIO_PuPd=GPIO_NOPULL
PE9.GPIO_Speed=GPIO_SPEED_FREQ_MEDIUM
PE9.Mode=SAI_B_MasterWithClock
PE9.Signal=SAI1_FS_B
PF0.GPIOParameters=GPIO_Speed,GPIO_PuPdOD,GPIO_Label
PF0.GPIO_Label=MCU_I2C2_SDA
PF0.GPIO_PuPdOD=GPIO_NOPULL
PF0.GPIO_Speed=GPIO_SPEED_FREQ_HIGH
PF0.Mode=I2C
PF0.Signal=I2C2_SDA
PF1.GPIOParameters=GPIO_Speed,GPIO_PuPdOD,GPIO_Label
PF1.GPIO_Label=MCU_I2C2_SCL
PF1.GPIO_PuPdOD=GPIO_NOPULL
PF1.GPIO_Speed=GPIO_SPEED_FREQ_HIGH
PF1.Mode=I2C
PF1.Signal=I2C2_SCL
PF10.Mode=Dual Bank
PF10.Signal=QUADSPI_CLK
PF11.GPIOParameters=GPIO_Label
PF11.GPIO_Label=MCU_BNO085_SEL_OUT
PF11.Signal=GPIO_Output
PF12.GPIOParameters=GPIO_Label
PF12.GPIO_Label=MCU_EXTI12_SX_DIO2_TXRXSW
PF12.Signal=GPXTI12
PF13.GPIOParameters=GPIO_Label
PF13.GPIO_Label=MCU_EXTI13_BNO085
PF13.Signal=GPXTI13
PF14.GPIOParameters=GPIO_Label
PF14.GPIO_Label=MCU_AX_SEL_OUT
PF14.Signal=GPIO_Output
PF15.GPIOParameters=GPIO_Label
PF15.GPIO_Label=MCU_SX_SEL_OUT
PF15.Signal=GPIO_Output
PF3.GPIOParameters=GPIO_Label
PF3.GPIO_Label=MCU_EXTI3_PEXPA
PF3.Signal=GPXTI3
PF4.GPIOParameters=GPIO_Label
PF4.GPIO_Label=MCU_EXTI4_PEXPB
PF4.Signal=GPXTI4
PF5.GPIOParameters=GPIO_Label
PF5.GPIO_Label=MCU_VBUS_SOFT_SW_EN_OUT
PF5.Signal=GPIO_Output
PF6.GPIOParameters=GPIO_PuPd,GPIO_Label
PF6.GPIO_Label=MCU_TIMCAP_PN
PF6.GPIO_PuPd=GPIO_PULLDOWN
PF6.Signal=S_TIM5_CH1
PF7.GPIOParameters=GPIO_PuPd,GPIO_Label
PF7.GPIO_Label=MCU_TIMCAP_VSOL

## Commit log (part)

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2018-09-26 HW_ARDUINO - schematic and board files added
2018-09-27 HW_ARDUINO - Raspberry Pi socket added, also - 2x20_SOCKET added
2018-09-27 HW_ARDUINO - Interconnect between PI socket and Arduino sockets added
2018-09-27 HW_ARDUINO - last positioning and small fixes
2018-09-27 HW_ARDUINO - CAM - job for exporting two layers added
2018-09-27 HW_ARDUINO - CAM - correction: some labels moved
2018-09-30 SW - Controller - task_TCXO_20MHz module refactored for central controlling
2018-09-30 SW - Controller - task_Si5338 module refactored for central controlling
2018-09-30 SW - Controller - task_ax5243 and task_sx1276 modules refactored for central controlling
2018-10-02 SW - tasks now ready and running cyclic timers on request
2018-10-03 SW - task_Hygro - running its timer and distibuting to task_LCD
2018-10-03 DOCS - MPU-9250 replaced by ICM-20948
2018-10-03 HW_1V1 - CAD/Eagle - Replacements for 9-axis controller and 1.8V supply
2018-10-07 SW - code generation - switched to separate peripheral *.c and *.h init files, all free pins are set to analog, enable full assert, application structure: basic
2018-10-07 SW - minSetup sub-project moved out of old directory structure
2018-10-07 SW - minSetup - .cproject update
2018-10-08 SW - adaptions to the new export scheme
2018-10-09 SW - patch file created for Core/Src/sai.c
2018-10-09 SW - usb_device - block disable fixed
2018-10-09 SW - StartxxxTask() hookes connected
2018-10-09 SW - Debug - switched -Os back to -O0 optimization
2018-10-09 SW - power reduction: modules do init theirselves - usb done
2018-10-10 SW - TrueSTUDIO_old - directory no more needed
2018-10-10 DOCS - 9-axis-MEMS motion tracking devices (w/ at least SPI-interface) added
2018-10-11 DOCS - 12_ADC - decission for HW_1V1 made
2018-10-12 DOCS - shorting filepathname
2018-10-12 DOCS - 18_WeatherSensors - directory structure changed
2018-10-12 DOCS - 18_WeatherSensors - directory structure changed (2)
2018-10-12 DOCS - 20_LED - decission done for component used in V1.1
2018-10-12 DOCS - 22_ElectronicSwitch - decission made for components used in HW-V1.1
2018-10-12 DOCS - 23_PMIC - 3V3V-->1V2 converter used for HW-V1.1
2018-10-13 SW - first changes for variable clock setup done
2018-10-14 DOCS - 24_ClockTiming_PLL - decission for HW_1V1 made
2018-10-14 DOCS - 26_OPs - decission for HW_1V1 made
2018-10-14 DOCS - 32_Buttons - decission for HW_1V1 made
2018-10-14 DOCS - directory substructure modified
2018-10-14 DOCS - 36_Crystals - decission for HW_1V1 made
2018-10-14 DOCS - 41_SMA-sockets - decission for HW_1V1 made
2018-10-14 DOCS - 45_UMC-Jacks - decission for HW_1V1 made
2018-10-14 DOCS - 47_Inductivities - decission for HW_1V1 made
2018-10-14 DOCS - 27_Logic-SerPar - decission for HW_1V1 made
2018-10-14 SW - clocking - module task_TCXO_20MHz fixed
2018-10-14 HW_1V0 - CAD/Eagle - AX5243 clock out is 8MHz
2018-10-14 SW - AX5243 - clock output changed from 1MHz to 8MHz
2018-10-15 HW_1V1 - CAD/Eagle - remove many signals from MCU switchboard
2018-10-15 SW - timer - hunting for PCLK bug
2018-10-16 SW - timer - 80MHz_MSI16_PLL ok
2018-10-16 SW - timer - 8MHz_MSI ok
2018-10-16 SW - timer - 80MHz_HSE10 ok
2018-10-16 SW - timer - stripped code re-added
2018-10-17 HW_1V1 - CAD/Eagle/lbr - df4iah_adc.lbr and df4iah_dac.lbr packages SSOP-20, SSOP-28, SSOP-30 added
2018-10-17 HW_1V1 - CAD/Eagle/lbr - df4iah_dac.lbr device WM8523 added
2018-10-18 DOCS - 14_EEPROM - decission for HW_1V1 made
2018-10-18 HW_1V1 - CAD/Eagle/lbr - df4iah_memory device CAT24C64 serial EEPROM 8kx8 I2C added
2018-10-18 SW_1V1 - TrueSTUDIO - re-configured pin arrangement for HW_1V1 done
2018-10-19 HW_1V1 - CAD/Eagle/lbr - df4iah_lcd device MIDAS MCCOG21605B6W-FPTLWI I2C added
2018-10-19 SW_1V1 - MCU pin planning - I2C3 and I2C4 made free
2018-10-20 SW_1V1 - MCU pin planning - dropped some lines to establish QUADSPI bank 1
2018-10-20 SW_1V1 - MCU pin planning - dual QUADSPI bank 1/2 prepared
2018-10-20 DOCS - 16_VHF-UHF_TRX - directory moved
2018-10-20 DOCS - 13_DAC - device manufacturer changed
2018-10-20 HW_1V1 - CAD/Eagle - device IS25LP032D serial FLASH added
2018-10-20 HW_1V1 - CAD/Eagle/lbr - value field of DAC WM8523 removed
2018-10-20 HW_1V1 - CAD/Eagle - current BOM file update
2018-10-21 HW_1V1 - CAD/Eagle/lbr - RGB-LED ASMT-YTB7-0AA02 added
2018-10-21 HW_1V1 - CAD/Eagle/lbr - text size changed for package
2018-10-21 HW_1V1 - CAD/Eagle/lbr - BQ25570 device added to df4iah_powersupply.lbr
2018-10-21 DOCS - 28_Prog-Resistors - MCP4661-104E/ST 100kR I2C pot added
2018-10-21 HW_1V1 - CAD/Eagle/lbr - device MCP4661 added to df4iah_dig-pot.lbr
2018-10-21 SW_1V1 - multiple pin changes done in cooperation with HW_1V1
2018-10-22 HW_1V1 - CAD/Eagle - PMIC 3.3V --> 1.20V - 2x dig. pot. for Vcore voltage reduction added
2018-10-22 HW_1V1 - CAD/Eagle - PMIC 3.3V --> 1.20V - I2C address added to the list
2018-10-22 HW_1V1 - CAD/Eagle - BME680 and BNO085_LGA28 added to the schematic
2018-10-22 HW_1V1 - CAD/Eagle - BNO085 - missing I2C termination added
2018-10-23 HW_1V1 - CAD/Eagle - Audio ADC - some wires moved
2018-10-23 HW_1V1 - CAD/Eagle - SX1262 device added to its page
2018-10-23 HW_1V1 - CAD/Eagle - SX1262 placed, SIM868 prepared
2018-10-23 DOCS - 29_GSM-LTE-GPS - SIM868 added
2018-10-24 HW_1V1 - CAD/Eagle - idea for SIM868 level shifter and LiPo charger added
2018-10-24 DOCS - 30_LevelShifters - double document removed
2018-10-24 DOCS - 29_GSM-GPRS_GNSS - decission for HW_1V1 made
2018-10-24 HW_1V1 - CAD/Eagle - I2C address map update, decission for LiPo charger made
2018-10-25 HW_1V1 - CAD/Eagle - I2C port expander instead of serial shift register
2018-10-26 HW_1V1 - CAD/Eagle/lbr - ic-packages.lbr update
2018-10-26 HW_1V1 - CAD/Eagle - I2C port expander moved to page 30
2018-10-26 HW_1V1 - CAD/Eagle - device BQ24193 added
2018-10-27 DOCS - 38_ElectricDoubleLayer-C - decission for HW_1V1 made
2018-10-27 HW_1V1 - CAD/Eagle/lbr - df4iah_rcl.lbr - Resistor array (8x) added
2018-10-27 HW_1V1 - CAD/Eagle/lbr - df4iah_opamp.lbr - device LPV811 added
2018-10-27 DOCS - 23_PMIC - own crafted spread sheet added for BQ25570
2018-10-28 HW_1V1 - CAD/Eagle - device LM53603-Q1 added
2018-10-28 HW_1V1 - CAD/Eagle - two level shifters added for SIM868 connection
2018-10-28 HW_1V1 - CAD/Eagle - device SIM868 added to its page
2018-10-28 HW_1V1 - CAD/Eagle/lbr - df4iah_diode.lbr - font size adjusted to 24 mils
2018-10-28 HW_1V1 - CAD/Eagle - some placement adjustments done
2018-10-29 HW_1V1 - CAD/Eagle/lbr - symbol changed for SIM868 device in df4iah_gsm.lbr
2018-10-29 HW_1V1 - CAD/Eagle - 2.2uH changed to IHLP2525SCZER2R2M01 device
2018-10-29 HW_1V1 - CAD/Eagle/lbr - df4iah_rcl.lbr - some L's added
2018-10-29 HW_1V1 - CAD/Eagle - I2C port expanders placed
2018-10-30 DOCS - 55_Inductivities - 2.2uH inductor added
2018-10-30 HW_1V1 - CAD/Eagle - placement of PMICs continued
2018-10-31 HW_1V1 - CAD/Eagle - page 18 placed
2018-10-31 DOCS - CAD/Eagle/lbr - 15uH device added to df4iah_rcl.lbr
2018-10-31 HW_1V1 - CAD/Eagle - SX1262 device values added
2018-11-01 HW_1V1 - CAD/Eagle - HARWIN connectors fixed
2018-11-02 HW_1V1 - CAD/Eagle - SIM868: first signals connected
2018-11-02 SW_1V1 - Update of *.ioc file
2018-11-02 HW_1V1 - CAD/Eagle - SIM868 integration continued
2018-11-03 SW_1V1 - Naming convention changed
2018-11-03 SW_1V1 - some more pins moved
2018-11-03 HW_1V1 - CAD/Eagle - many signal names changed, SIM868 continued to implement
2018-11-04 HW_1V1 - CAD/Eagle/lbr - SAW-filter added to df4iah_rf.lbr
2018-11-04 HW_1V1 - CAD/Eagle/lbr - E-Ink Display added to df4iah_lcd.lbr
2018-11-04 HW_1V1 - CAD/Eagle - all pages placed, E-Ink Display still to improve
2018-11-05 HW_1V1 - CAD/Eagle - E-Ink Display placed and RESET button moved
2018-11-05 HW_1V1 - CAD/Eagle - ERC done
2018-11-05 DOCS - 36_OPs - OPA381 added
2018-11-06 DOCS - 36_OPs - OPA381 Spice model added
2018-11-07 HW_1V1 - CAD/Eagle - 3mm margins added to PCB
2018-11-07 HW_1V1 - CAD/Eagle/lbr - df4iah_rf.lbr - packages fixed
2018-11-07 HW_1V1 - CAD/Eagle - many resistors and capacitors changed to 0402 package
2018-11-08 HW_1V1 - CAD/Eagle - current libraries reloaded, border lines made smooth
2018-11-08 HW_1V1 - CAD/Eagle - schematic pages re-ordered
2018-11-09 HW_1V1 - CAD/Eagle - VDDUSB fixed at MCU schematic page
2018-11-10 HW_1V1 - CAD/Eagle/lbr - df4iah_lcd.lbr - LCD and E-Ink Display area changed
2018-11-10 DOCS - 09_Results/Pictures - V1.1 PCB after placement
2018-11-11 HW_1V1 - CAD/Eagle - pulling out all devices from the 3mm border area
2018-11-11 HW_1V1 - CAD/Eagle - cut-out polygons for BME680 renamed
2018-11-12 SW_1V1 - GPIO line for MCU_VBUS_SOFT_SW_EN_OUT added
2018-11-13 HW_1V1 - CAD/Eagle/lbr - LCD backlight pads fixed
2018-11-14 HW_1V1 - CAD/Eagle/lbr - df4iah_fiducial.lbr - text size adapted to standard size
2018-11-14 HW_1V1 - CAD/Eagle/lbr - df4iah_crystal.lbr - dimension for device fixed
2018-11-15 HW_1V1 - CAD/Eagle - C1955 added, routing of the day
2018-11-15 HW_1V1 - CAD/Eagle - Text size of new device fixed
2018-11-17 HW_1V1 - CAD/Eagle - Routing round the PLL
2018-11-20 HW_1V1 - CAD/Eagle - Some routing in the north done
2018-11-26 HW_1V1 - CAD/Eagle - Some routing in the wild west done
2018-11-30 HW_1V1 - CAD/Eagle - Short wires routing done
2018-12-02 HW_1V1 - CAD/Eagle - DRC findings solved
2018-12-03 HW_1V1 - CAD/Eagle - some routing in the south done
2018-12-04 HW_1V1 - CAD/Eagle - some more wires routed in the south
2018-12-10 HW_1V1 - CAD/Eagle - another day routed
2018-12-17 DOCS - Current routing image update 2018-12-17
2018-12-19 DOCS - Current routing image update 2018-12-19
2018-12-30 HW_1V1 - CAD/Eagle - Drills increased to 3.0mm from 2.8mm
2019-01-01 HW_1V1 - CAD/Eagle - STM32L496 symbol fixed
2019-01-11 HW_1V1 - CAD/Eagle - new board design settings due to change of PCB house
2019-01-11 HW_1V1 - CAD/Eagle - additional PMIC 5V0 --> 3V3 added
2019-01-11 HW_1V1 - CAD/Eagle - Solar power enable added
2019-01-14 HW_1V1 - CAD/Eagle - extra 5V-->3.3V switcher added
2019-01-16 SW_1V1 - MCU pinout - some more signals controlled by the MCU
2019-01-17 HW_1V1 - CAD/Eagle - update of schematic and board due to library changes of STM32L4
2019-01-23 HW_1V1 - CAD/Eagle - routing of the day (23.01.)
2019-01-28 HW_1V1 - CAD/Eagle - routing around LoRa chip
2019-01-30 HW_1V1 - CAD/Eagle - QUADSPI routed
2019-01-31 HW_1V1 - CAD/Eagle - SPI3 routed
2019-02-01 HW_1V1 - df4iah_connector.lbr - SWD connector fixed
2019-02-11 HW_1V1 - CAD/Eagle - 32kHz crystal oscillator modified
2019-02-12 HW_1V1 - CAD/Eagle/lbr - df4iah_powersupply package SOT95P280X145-5N text size fixed
2019-02-12 HW_1V1 - CAD/Eagle/lbr - df4iah_connector SWD-connector restring change
2019-02-13 HW_1V1 - CAD/Eagle/lbr - df4iah_powersupply VQFN-24.pac, HTSSOP16.pac drill size expanded to 12mil (0.3mm)
2019-02-13 HW_1V3 - CAD/Eagle/lbr - df4iah_osc QFN24_P0MM5CTRPAD.pac modified
2019-02-13 HW_1V1 - CAD/Eagle - routing under the MCU
2019-02-20 HW_1V1 - CAD/Eagle - Today some more routing in the mid-south
2019-02-22 SW_1V1 - new power calculations
2019-02-25 SW_1V1 - HSMA setup with 1.3.0 upgrade (2)
2019-02-25 HW_1V1 - CAD/Eagle - MCU east complete
2019-02-25 HW_1V1 - CAD/Eagle - MCU west complete
2019-02-25 HW_1V1 - CAD/Eagle - CLK0 bus routed
2019-02-28 HW_1V1 - CAD/Eagle/lbr - df4iah_stm32l4.lbr STM32Ll452RE added
2019-03-01 HW_1V1 - CAD/Eagle/lbr - updates for df4iah_powersupply, df4iah_rcl and df4iah_stm32l4
2019-03-03 HW_1V1 - CAD/Eagle/lbr - df4iah_memory.lbr FRAM FEDR44V064B-02 added
2019-03-03 HW_1V1 - CAD/Eagle/lbr - df4iah_rf.lbr SX1261 added
2019-03-04 HW_1V1 - CAD/Eagle/lbr - df4iah_connector.lbr Phoenix 1990067 added
2019-03-05 HW_1V1 - CAD/Eagle/lbr - df4iah_rf.lbr ESP8266EX added
2019-03-07 HW_1V1 - CAD/Eagle/lbr - df4iah_rf.lbr ESP-12F added
2019-03-09 HW_1V1 - CAD/Eagle/lbr - df4iah_rf.lbr ESP-12F pin directions fixed
2019-03-11 HW_1V1 - remove mis-merge with master
2019-03-11 HW_1V1 - CAD/Eagle - escaping of both IO expanders done
2019-03-12 HW_1V1 - CAD/Eagle - all micro airwires fixed
2019-03-12 DOCS - lost directory structure re-established
2019-03-12 DOCS - Routing finished (2019-03-12)
2019-03-12 DOCS - 09_Results - Manufacturing by Beta-Layout
